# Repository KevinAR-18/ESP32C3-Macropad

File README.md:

# KeyBloom

KeyBloom is a Windows desktop companion for a custom ESP32-C3 macro pad. It provides a PySide6-based interface to configure multiple profiles, map each hardware button to a keyboard shortcut or application launcher, and keep the app running in the system tray while listening to serial events from the device.

## Features

- 5 configurable profiles
- 6 slots per profile
- Keyboard shortcut capture with presets
- Media key capture support, including fallback for `Fn`-based media keys
- Application launcher per slot
- ESP32 serial auto-detection with reconnect retry/backoff
- USB-priority transport with verified handshake and heartbeat
- BLE scan/connect/disconnect/forget inside KeyBloom, with saved-device reconnect
- BLE idle power reduction and encoder-1-only deep-sleep wake
- System tray mode for background runtime
- Windows startup integration with start-minimized tray behavior
- Default startup page always returns to Profile 1
- Settings stored in `%APPDATA%\KeyBloom\settings.json`
- Spotify session volume control for the second encoder
- KiCad PCB files included in the repository
- ESP32-C3 firmware source included in the repository

## Project Structure

- [main.py](./main.py): application entry point and main runtime logic
- [keybloom.ui](./keybloom.ui): Qt Designer source file
- [ui/ui_keybloom.py](./ui/ui_keybloom.py): generated Qt UI file
- [ui/preview_button.py](./ui/preview_button.py): custom keycap preview widget
- [ui/ui_functions.py](./ui/ui_functions.py): borderless window and drag helpers
- [config/settings_manager.py](./config/settings_manager.py): settings load/save and profile serialization
- [input/key_capture.py](./input/key_capture.py): shortcut capture event filter
- [input/shortcut_utils.py](./input/shortcut_utils.py): shortcut normalization helpers
- [serial_tools/port_detector.py](./serial_tools/port_detector.py): serial port auto-detection helpers
- [connection/manager.py](./connection/manager.py): background USB/BLE transport and connection policy
- [connection/dialog.py](./connection/dialog.py): connection and power settings dialog
- [utils/date_utils.py](./utils/date_utils.py): clock/date formatting helper
- [resources.qrc](./resources.qrc): Qt resource manifest
- [resources_rc.py](./resources_rc.py): generated Qt resource module
- [build.bat](./build.bat): main PyInstaller build script
- [KeyBloom.spec](./KeyBloom.spec): PyInstaller spec file
- [examplebuildbat.bat](./examplebuildbat.bat): simplified build example
- [PCB_Macropad/Macropad_PCB](./PCB_Macropad/Macropad_PCB): KiCad project for the macro pad PCB
- [ProgramESP32C3_Macropad/ProgramESP32C3_Macropad.ino](./ProgramESP32C3_Macropad/ProgramESP32C3_Macropad.ino): ESP32-C3 firmware source
- [bluetooth_test](./bluetooth_test): isolated ESP32-C3 BLE communication prototype for Windows 11

## Requirements

- Windows
- Python 3.12+ recommended
- A virtual environment in `.venv`
- ESP32-C3 macro pad firmware that sends serial messages compatible with the app

Install dependencies:

```powershell
.venv\Scripts\python.exe -m pip install -r requirements.txt
```

## Running From Source

```powershell
.venv\Scripts\python.exe main.py
```

## Runtime Behavior

- When Auto Startup is enabled, Windows launches KeyBloom with a start-minimized flag so the app goes directly to the system tray.
- When the main window is opened manually, the app always starts on Profile 1.
- Shortcut capture uses the Qt event path first and temporarily enables a global keyboard hook while recording, which improves capture for media keys such as `Media Next` and `Media Previous`.
- Serial auto-detect keeps retrying with a reconnect backoff when the ESP32-C3 disconnects or re-enumerates.

## Settings Location

At runtime, the app saves settings to:

```text
%APPDATA%\KeyBloom\settings.json
```

Legacy settings next to the executable or project folder are still readable as fallback.

## Build EXE

Install PyInstaller first:

```powershell
.venv\Scripts\python.exe -m pip install pyinstaller
```

Then run:

```powershell
build.bat
```

Expected output:

```text
dist\KeyBloom.exe
dist\icon.ico
```

`build.bat` also copies `icon.ico` into `dist\` after a successful build.

## Hardware Files

The repository also includes the hardware design files for the macro pad PCB.

- The KiCad project is located in [PCB_Macropad/Macropad_PCB](./PCB_Macropad/Macropad_PCB).
- The PCB design files are already prepared for production and intended for JLCPCB workflow.
- The project includes the schematic, PCB layout, and backup archives generated during board iteration.

## ESP32-C3 Firmware

### Dual USB/BLE setup

Upload `ProgramESP32C3_Macropad/ProgramESP32C3_Macropad.ino` with
**NimBLE-Arduino 2.x** installed. Compilation has been checked with Arduino-ESP32
**3.3.10**, target `esp32:esp32:esp32c3:CDCOnBoot=cdc` (native USB CDC enabled).
Choose the board/USB settings matching your actual hardware. Close Serial Monitor
before connecting KeyBloom. Update both desktop app and firmware together: the old
serial firmware and BLE test firmware do not implement the production handshake/control protocol.

Open **Settings → USB / Bluetooth Connection…**, or **Connection…** in the tray menu.

1. For USB, enable Auto Detect (or enter the COM port manually). KeyBloom verifies
   the device before selecting USB. An open COM port alone is not sufficient.
2. For BLE, click **Scan**, select `KeyBloom-C3`, then **Connect**. Use the KeyBloom
   dialog rather than Windows Bluetooth pairing. The device is saved only after
   the BLE service, control write, and event subscription succeed.
3. Saved devices reconnect on app startup and after an unexpected disconnection.
4. **Disconnect** keeps the device saved and disables reconnect, including after
   an app restart. **Connect** enables it again. **Forget device** removes the saved device.
5. USB takes priority. Removing USB permits BLE reconnect unless manually disconnected.
   A charging cable without an active KeyBloom data connection does not select USB.

The board needs battery/another power source to keep running when USB is removed.
The prototype BLE client must be closed before connecting the desktop app.

### Custom button and rotary actions

- On any profile page, click **Edit button & rotary actions…** or click a button
  preview and choose **Edit Action…**.
- Each profile has 12 mappings: six buttons and left/right/click for each rotary.
- Available actions: keyboard shortcut, media (play/pause, next, previous, stop),
  system audio, Spotify volume, open app/file/folder, URL, text, switch profile,
  and None. Spotify volume steps can be set from 1% to 100%.
- Text preserves whitespace and is typed into the focused application. Media
  controls use the Windows media session; they are not Spotify-specific.
- **Copy/Paste** copies one mapping. The profile selector copies all 12 mappings
  from another profile. **Export/Import profile** uses a portable JSON file.
  Imported/copied changes take effect only after **Save**; Cancel discards them.
- Mappings are saved in the application's settings and restored on restart.
  Existing button mappings and the original rotary defaults are retained.
- Firmware currently repeats held buttons; briefly press toggle actions such
  as Play/Pause and profile switching. Long/double press are not available yet.

### Power and wake-up behavior

- Default: after **60 seconds** of physical inactivity, request longer BLE connection
  intervals/slave latency and slower advertising when disconnected. The central
  (Windows) can negotiate different connection parameters.
- Stock Arduino-ESP32 3.3.10 in this environment has `CONFIG_PM_ENABLE` and
  `CONFIG_BT_CTRL_MODEM_SLEEP` disabled. This build reduces CPU speed to **80 MHz**
  while idle and restores **160 MHz** on activity/USB. It does **not** claim connected
  automatic light-sleep. Custom cores with compatible PM/modem-sleep/tickless-idle
  support can use the guarded PM configuration in the sketch.
- Default: after **600 seconds**, enter deep sleep and disconnect BLE. This also
  applies when advertising without a connected client. Active USB heartbeat prevents sleep.
- **Only clicking encoder 1 (GPIO 5) wakes from deep sleep.** Rotation and other
  buttons do not wake it. The complete wake click, including hold/repeat, is consumed;
  release it before using encoder 1 again.
- KeyBloom reconnects to a waking saved device unless Disconnect was selected.
  A sleeping board cannot be woken by the app's Connect button. Click encoder 1 first.
- USB plug-in wake depends on the board's power/reset wiring; do not assume it wakes
  an already battery-powered sleeping board. Use encoder 1 if needed.
- Change timings or disable deep sleep with **Save power settings**. Settings are saved
  in AppData and sent on connection; firmware persists changed power settings in NVS.
- Sleep status is shown when the firmware's notification reaches the app. A silent
  disconnect cannot reliably be identified as sleep. Reconnect scanning backs off to 30 seconds.

Hardware verification is still required: measure board current in active/idle/deep-sleep
states, confirm GPIO 5 remains pulled high when released, exercise wake/reconnect and
USB hot-plug, and check that LED/regulator consumption meets your battery-life needs.
Do not infer battery life from firmware sleep mode alone.

### Protocol and validation

BLE name/service/event UUID remain compatible with the prototype. Production adds
the writable control characteristic `7c3a0003-8f6e-4d4b-a8f3-6f8f9c1b0001`.

- USB: `KB HELLO <session>` → `KB READY <session>`.
- Heartbeat every second: `KB PING <session>` → `KB PONG <session>`; 3-second lease.
- Graceful release: `KB BYE <session>`.
- Power configuration: `KB POWER <0|1> <idle_seconds> <sleep_seconds>` over USB or BLE.
- Before deep sleep: BLE notification `KB SLEEP` (best effort).

Run desktop policy tests and the isolated UI smoke check:

```powershell
.venv\Scripts\python.exe -m unittest discover -s tests -v
.venv\Scripts\python.exe tests\smoke_ui.py
```

The ESP32-C3 firmware is already included in the repository:

- Firmware source: [ProgramESP32C3_Macropad/ProgramESP32C3_Macropad.ino](./ProgramESP32C3_Macropad/ProgramESP32C3_Macropad.ino)
- The desktop app expects the board firmware to send serial messages that match the event format documented below.

## Serial Event Format

The app currently reacts to messages such as:

```text
BUTTON 1 PRESSED
ENC1 RIGHT
ENC1 LEFT
ENC1 BUTTON PRESSED
ENC2 RIGHT
ENC2 LEFT
ENC2 BUTTON PRESSED
START
```

## Notes

- The UI is generated from `keybloom.ui`, but runtime optimizations are handled in Python code.
- The app is tuned to stay lighter while minimized to tray by reducing unnecessary timers, delayed widget setup, and lazy-loading heavy modules.
- `requirements.txt` is kept intentionally small to match the runtime dependencies used by the current app.

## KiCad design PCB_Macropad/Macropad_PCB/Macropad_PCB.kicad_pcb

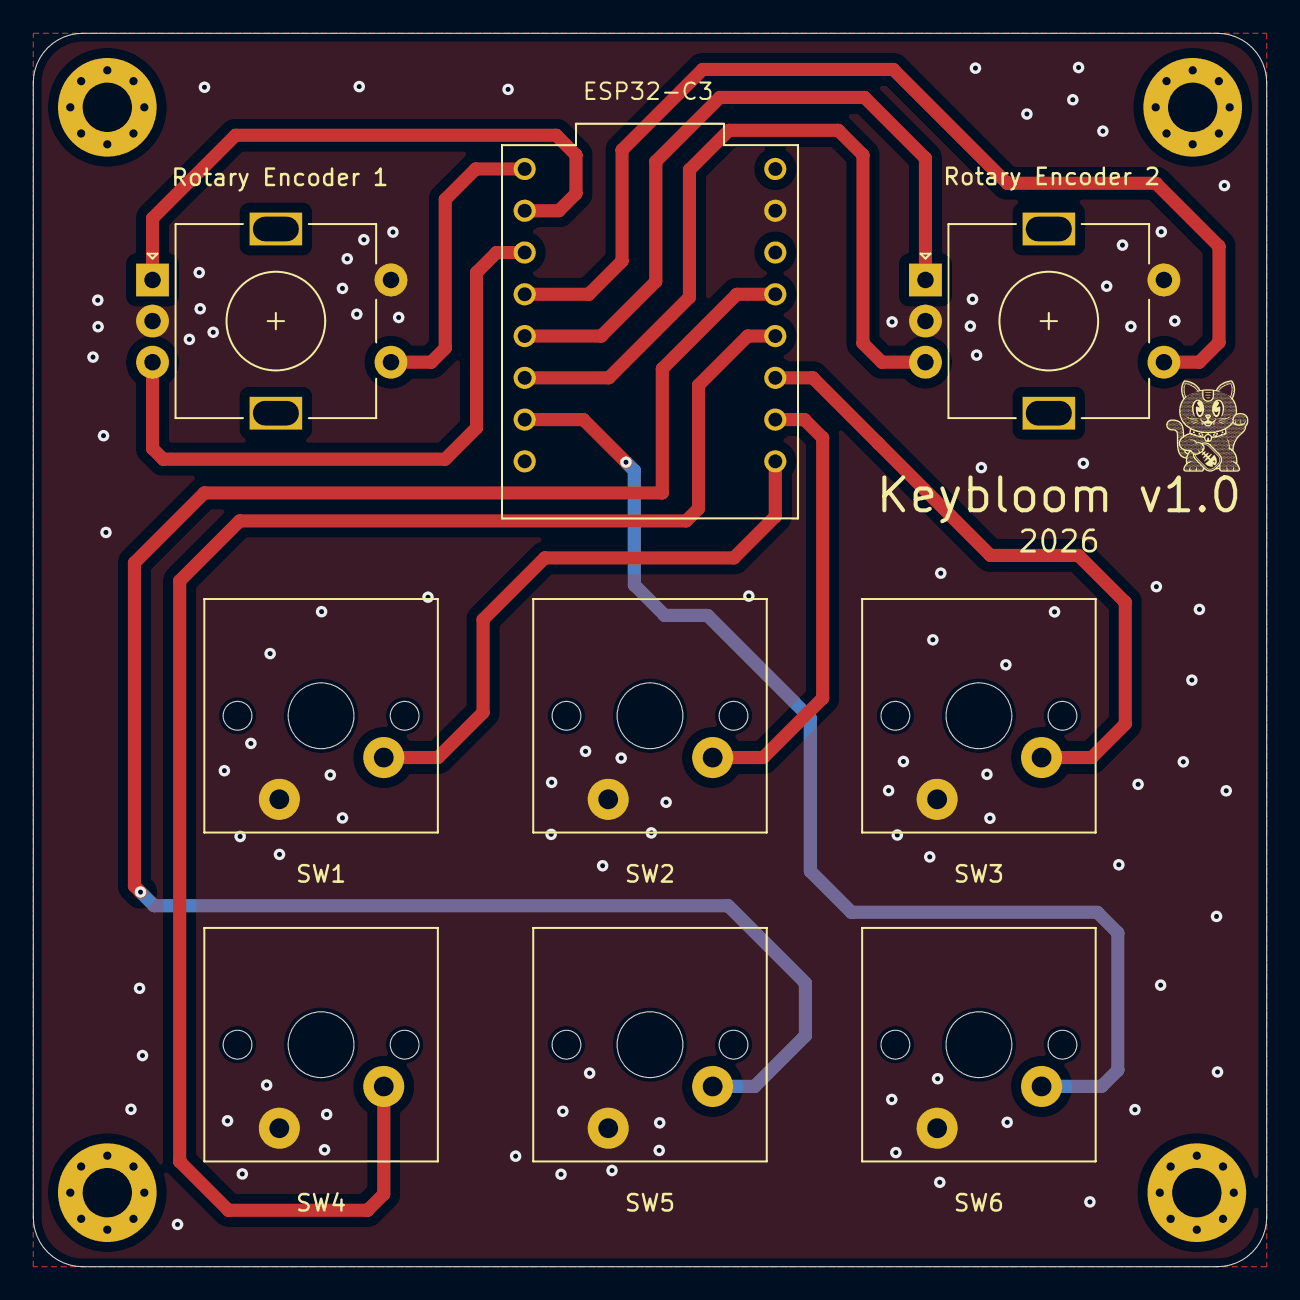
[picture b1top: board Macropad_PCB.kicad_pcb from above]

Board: 2 copper layers, 75.0 x 75.0 mm, 13 parts (0 on the bottom side), 13 nets.

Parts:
ESP32-C3: ESP32-C3; MODULE_ESP32-C3_SUPERMINI_TH
H3, H4, H5, H6: MountingHole; MountingHole_3mm_Pad_Via
Rotary Encoder 1: Rotary Encoder Switch 1; RotaryEncoder_Alps_EC11E-Switch_Vertical_H20mm
Rotary Encoder 2: Rotary Encoder Switch 2; RotaryEncoder_Alps_EC11E-Switch_Vertical_H20mm
SW1: Button 1; SW_Cherry_MX_PCB_1.00u
SW2: Button 2; SW_Cherry_MX_PCB_1.00u
SW3: Button 3; SW_Cherry_MX_PCB_1.00u
SW4: Button 4; SW_Cherry_MX_PCB_1.00u
SW5: Button 5; SW_Cherry_MX_PCB_1.00u
SW6: Button 6; SW_Cherry_MX_PCB_1.00u

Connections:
D0: ESP32-C3.0 (GPIO0), SW1.1 (A)
D1: ESP32-C3.1 (GPIO1), SW2.1 (A)
D2: ESP32-C3.2 (GPIO2), SW3.1 (A)
D3: ESP32-C3.3 (GPIO3), SW4.1 (A)
D4: ESP32-C3.4 (GPIO4), SW5.1 (A)
D5: ESP32-C3.5 (GPIO5), Rotary Encoder 1.S1
D6: ESP32-C3.6 (GPIO6), Rotary Encoder 1.A
D7: ESP32-C3.7 (GPIO7), Rotary Encoder 1.B
D8: ESP32-C3.8 (GPIO8), Rotary Encoder 2.S1
D9: ESP32-C3.9 (GPIO9), Rotary Encoder 2.A
D10: ESP32-C3.10 (GPIO10), Rotary Encoder 2.B
D20: ESP32-C3.20 (GPIO20), SW6.1 (A)
GND: ESP32-C3.G (GND), Rotary Encoder 1.C, Rotary Encoder 1.S2, Rotary Encoder 2.C, Rotary Encoder 2.S2, SW1.2 (B), SW2.2 (B), SW3.2 (B), SW4.2 (B), SW5.2 (B), SW6.2 (B)

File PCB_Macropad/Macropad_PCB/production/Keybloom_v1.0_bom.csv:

Designator,Footprint,Quantity,Value,LCSC Part #
ESP32-C3,MODULE_ESP32-C3_SUPERMINI_TH,1,ESP32-C3,
ROTARY ENCODER 1,RotaryEncoder_Alps_EC11E-Switch_Vertical_H20mm,1,Rotary Encoder Switch 1,
ROTARY ENCODER 2,RotaryEncoder_Alps_EC11E-Switch_Vertical_H20mm,1,Rotary Encoder Switch 2,
SW1,SW_Cherry_MX_PCB_1.00u,1,Button 1,
SW2,SW_Cherry_MX_PCB_1.00u,1,Button 2,
SW3,SW_Cherry_MX_PCB_1.00u,1,Button 3,
SW4,SW_Cherry_MX_PCB_1.00u,1,Button 4,
SW5,SW_Cherry_MX_PCB_1.00u,1,Button 5,
SW6,SW_Cherry_MX_PCB_1.00u,1,Button 6,

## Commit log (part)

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2025-12-30 Initmacropad
2025-12-30 UpdateButtondanRotary
2025-12-30 Updatecobacoba
2025-12-31 updateealrygui
2025-12-31 updateguimalamtahunbaru:)
2026-01-01 update gui
2026-01-01 update gui lagi
2026-02-07 update latest
2026-04-14 Add netlist file for PCB Macropad with detailed component connections
2026-04-15 Remove obsolete files for Keybloom v1.0 production, including design files, BOM, and netlist.
2026-04-15 Add .gitignore file to exclude production files and backups from version control
2026-04-15 Remove unused files and scripts from the project
2026-04-15 Refactor code structure for improved readability and maintainability
2026-04-15 Fix CSS property for checkbox font weight and update UI file reference
2026-04-15 Add additional __pycache__ files to .gitignore for cleaner version control
2026-04-19 Update .gitignore to exclude additional __pycache__ files and refactor main.py for improved structure and readability
2026-04-19 Refactor tray menu actions for improved clarity and organization
2026-04-19 Add Coba Button Preview and Transparent Keycap Preview
    - Implemented DemoWindow class in cobabutton.py for displaying keycap previews.
    - Created TransparentKeycapPreview class in preview_button.py for rendering individual keycap previews with animation effects.
    - Introduced modes for keycap previews: unset, application, and keyboard.
    - Added buttons to set the mode of all previews in the DemoWindow.
    - Enhanced visual styles for the UI components with custom stylesheets.
2026-04-20 Add lock file for Macropad PCB design
2026-04-20 feat: Enhance Spotify integration and serial communication
    - Added Spotify mode selection and API credentials input fields in the UI.
    - Updated settings management to include serial port configuration and Spotify settings.
    - Implemented serial communication for button presses and rotary encoder events.
    - Refactored settings loading and saving logic to accommodate new configurations.
    - Improved button handling and added functionality for Spotify volume control.
    - Updated .gitignore to exclude sensitive files and unnecessary cache files.
2026-04-22 Refactor MainWindow for lazy loading and improved memory management
    - Introduced lazy loading for keyboard, psutil, and pycaw modules to reduce startup overhead.
    - Increased SERIAL_POLL_MS from 25 to 40 for better serial communication stability.
    - Added a buffer limit for serial data to prevent memory overflow.
    - Removed unused Spotify UI elements to optimize memory usage.
    - Updated settings management to save in AppData for better permissions handling.
    - Enhanced error handling for module imports and serial communication.
2026-04-22 Remove example build script for KeyBloom
2026-04-22 feat: Add application icon support and update build script
2026-04-23 Tes Commit
2026-05-10 Add utility module and date handling functionality
    - Created a new utility module `__init__.py` for KeyBloom helpers.
    - Implemented `date_utils.py` with a `Date` class to update QLabel with current time and date.
2026-05-14 feat: Update .gitignore to exclude KeyBloom setup files
